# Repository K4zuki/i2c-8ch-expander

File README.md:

# i2c-8ch-expander
8-channel I2C mux, works at 125C

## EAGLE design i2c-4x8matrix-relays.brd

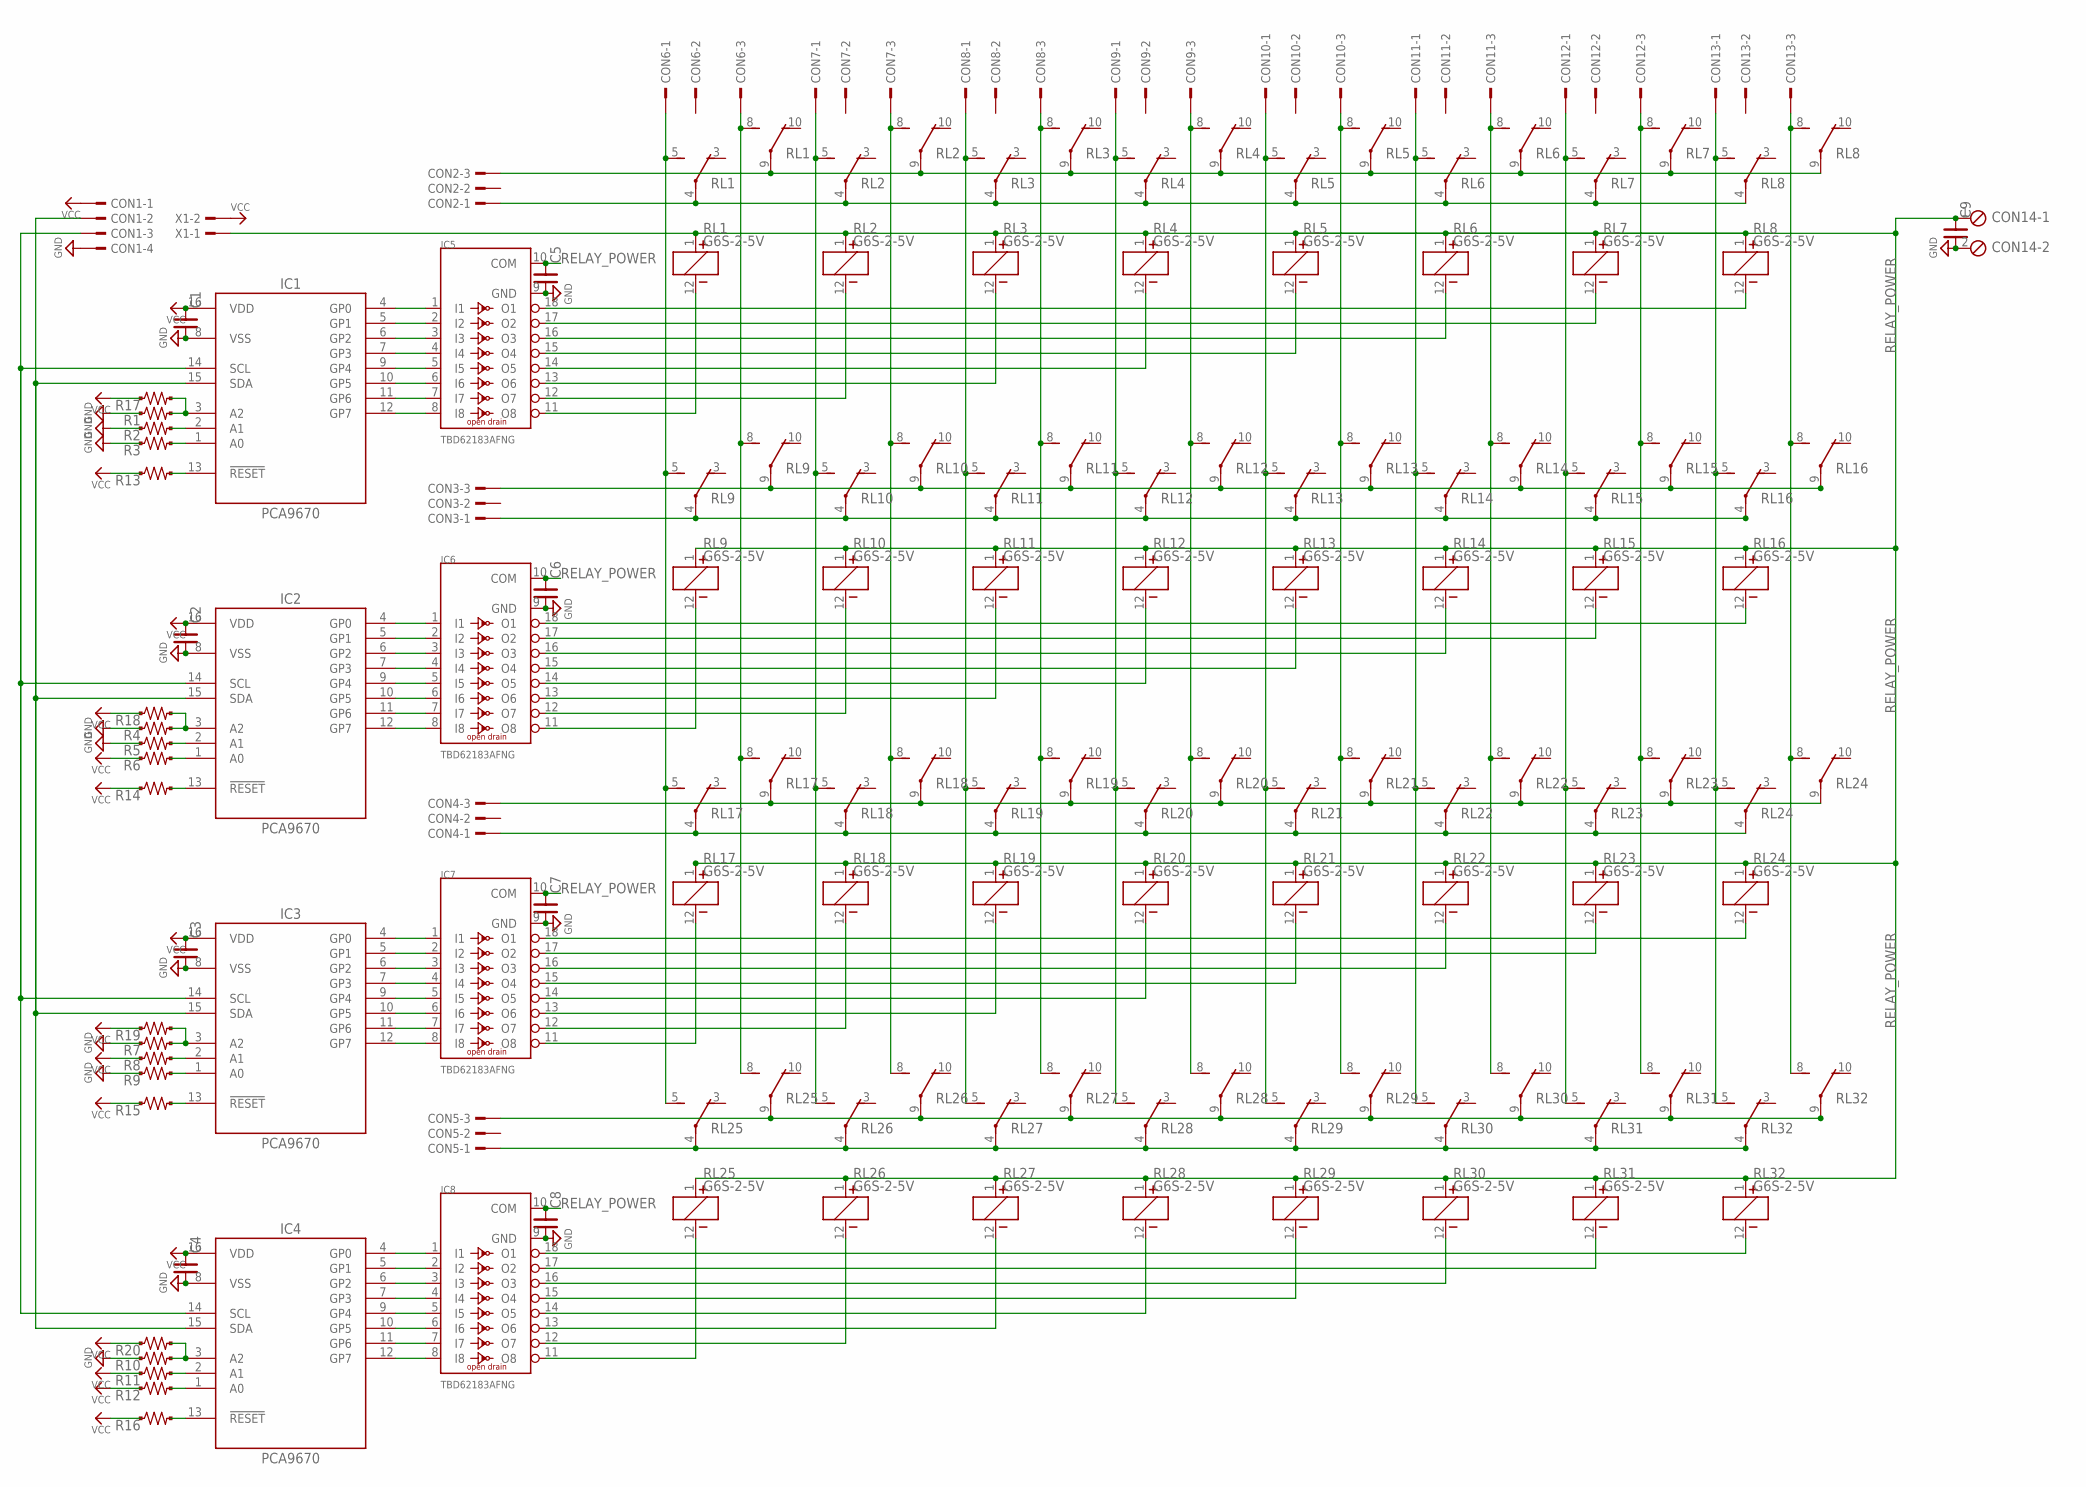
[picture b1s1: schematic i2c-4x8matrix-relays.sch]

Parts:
C1, C2, C3, C4, C5, C6, C7, C8: C-SMD-0.1U-1005; C0402
C9: C-SMD-10U-1608; CR-1608
CON1: S4B-XH-A; S4B-XH-A(LF)(SN)
CON2, CON3, CON4, CON5, CON6, CON7, CON8, CON9, CON10, CON11, CON12, CON13: S3B-XH-A; S3B-XH-A(LF)(SN)
CON14: ETB43024B; ETB43024
IC1, IC2, IC3, IC4: PCA9670; SOT65P510X450X110-16N
IC5, IC6, IC7, IC8: TBD62183AFNG; SOT65P640X440-18N
R1, R2, R3, R4, R5, R6, R7, R8, R9, R10, R11, R12, R13, R14, R15, R16: R-US--1005SHORT; R0402SHORT
R17, R18, R19, R20: R-US-10K-1005; C0402
RL1, RL2, RL3, RL4, RL5, RL6, RL7, RL8, RL9, RL10, RL11, RL12, RL13, RL14, RL15, RL16, RL17, RL18, RL19, RL20, RL21, RL22, RL23, RL24, RL25, RL26, RL27, RL28, RL29, RL30, RL31, RL32: G6S-2-5V; G6S-2
X1: PH-1X2SG

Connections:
GND: C1.2, C2.2, C3.2, C4.2, C5.2, C6.2, C7.2, C8.2, C9.2, CON1.4, CON14.2, IC1.8 (VSS), IC2.8 (VSS), IC3.8 (VSS), IC4.8 (VSS), IC5.9 (GND), IC6.9 (GND), IC7.9 (GND), IC8.9 (GND), R1.1, R1.2 (1), R2.1, R2.2 (1), R3.1, R3.2 (1), R4.1, R4.2 (1), R5.1, R5.2 (1), R7.1, R7.2 (1), R9.1, R9.2 (1), R10.1, R10.2 (1)
unnamed: CON3.1, RL9.4 (COM), RL10.4 (COM), RL11.4 (COM), RL12.4 (COM), RL13.4 (COM), RL14.4 (COM), RL15.4 (COM), RL16.4 (COM)
unnamed: CON4.1, RL17.4 (COM), RL18.4 (COM), RL19.4 (COM), RL20.4 (COM), RL21.4 (COM), RL22.4 (COM), RL23.4 (COM), RL24.4 (COM)
unnamed: CON2.1, RL1.4 (COM), RL2.4 (COM), RL3.4 (COM), RL4.4 (COM), RL5.4 (COM), RL6.4 (COM), RL7.4 (COM), RL8.4 (COM)
unnamed: CON2.3, RL1.9 (COM), RL2.9 (COM), RL3.9 (COM), RL4.9 (COM), RL5.9 (COM), RL6.9 (COM), RL7.9 (COM), RL8.9 (COM)
unnamed: CON6.1, RL1.5 (NO), RL9.5 (NO), RL17.5 (NO), RL25.5 (NO)
unnamed: CON7.1, RL2.5 (NO), RL10.5 (NO), RL18.5 (NO), RL26.5 (NO)
unnamed: CON3.3, RL9.9 (COM), RL10.9 (COM), RL11.9 (COM), RL12.9 (COM), RL13.9 (COM), RL14.9 (COM), RL15.9 (COM), RL16.9 (COM)
unnamed: CON4.3, RL17.9 (COM), RL18.9 (COM), RL19.9 (COM), RL20.9 (COM), RL21.9 (COM), RL22.9 (COM), RL23.9 (COM), RL24.9 (COM)
unnamed: IC8.18 (O1), RL32.12 (2)
unnamed: IC8.11 (O8), RL25.12 (2)
unnamed: CON8.1, RL3.5 (NO), RL11.5 (NO), RL19.5 (NO), RL27.5 (NO)
unnamed: CON9.1, RL4.5 (NO), RL12.5 (NO), RL20.5 (NO), RL28.5 (NO)
unnamed: IC1.4 (GP0), IC5.1 (I1)
unnamed: IC1.5 (GP1), IC5.2 (I2)
unnamed: IC1.6 (GP2), IC5.3 (I3)
unnamed: CON6.3, RL1.8 (NO), RL9.8 (NO), RL17.8 (NO), RL25.8 (NO)
unnamed: IC1.7 (GP3), IC5.4 (I4)
unnamed: IC1.9 (GP4), IC5.5 (I5)
unnamed: IC7.11 (O8), RL17.12 (2)
unnamed: CON7.3, RL2.8 (NO), RL10.8 (NO), RL18.8 (NO), RL26.8 (NO)
unnamed: CON9.3, RL4.8 (NO), RL12.8 (NO), RL20.8 (NO), RL28.8 (NO)
unnamed: CON8.3, RL3.8 (NO), RL11.8 (NO), RL19.8 (NO), RL27.8 (NO)
unnamed: CON5.1, RL25.4 (COM), RL26.4 (COM), RL27.4 (COM), RL28.4 (COM), RL29.4 (COM), RL30.4 (COM), RL31.4 (COM), RL32.4 (COM)
unnamed: CON5.3, RL25.9 (COM), RL26.9 (COM), RL27.9 (COM), RL28.9 (COM), RL29.9 (COM), RL30.9 (COM), RL31.9 (COM), RL32.9 (COM)
unnamed: CON10.1, RL5.5 (NO), RL13.5 (NO), RL21.5 (NO), RL29.5 (NO)
unnamed: CON10.3, RL5.8 (NO), RL13.8 (NO), RL21.8 (NO), RL29.8 (NO)
unnamed: CON11.1, RL6.5 (NO), RL14.5 (NO), RL22.5 (NO), RL30.5 (NO)
unnamed: CON11.3, RL6.8 (NO), RL14.8 (NO), RL22.8 (NO), RL30.8 (NO)
unnamed: CON12.1, RL7.5 (NO), RL15.5 (NO), RL23.5 (NO), RL31.5 (NO)
unnamed: CON12.3, RL7.8 (NO), RL15.8 (NO), RL23.8 (NO), RL31.8 (NO)
unnamed: CON13.1, RL8.5 (NO), RL16.5 (NO), RL24.5 (NO), RL32.5 (NO)
unnamed: CON13.3, RL8.8 (NO), RL16.8 (NO), RL24.8 (NO), RL32.8 (NO)
unnamed: IC1.10 (GP5), IC5.6 (I6)
unnamed: IC7.15 (O4), RL21.12 (2)
unnamed: IC7.18 (O1), RL24.12 (2)
unnamed: IC7.14 (O5), RL20.12 (2)
unnamed: IC7.12 (O7), RL18.12 (2)
unnamed: IC7.13 (O6), RL19.12 (2)
unnamed: IC7.16 (O3), RL22.12 (2)
unnamed: IC7.17 (O2), RL23.12 (2)
unnamed: IC1.11 (GP6), IC5.7 (I7)
unnamed: IC1.12 (GP7), IC5.8 (I8)
unnamed: IC2.4 (GP0), IC6.1 (I1)
unnamed: IC2.5 (GP1), IC6.2 (I2)
unnamed: IC2.6 (GP2), IC6.3 (I3)
unnamed: IC2.7 (GP3), IC6.4 (I4)
unnamed: IC2.9 (GP4), IC6.5 (I5)
unnamed: IC2.10 (GP5), IC6.6 (I6)
unnamed: IC2.11 (GP6), IC6.7 (I7)
unnamed: IC2.12 (GP7), IC6.8 (I8)
unnamed: IC3.4 (GP0), IC7.1 (I1)
unnamed: IC3.5 (GP1), IC7.2 (I2)
unnamed: IC3.6 (GP2), IC7.3 (I3)
unnamed: IC3.7 (GP3), IC7.4 (I4)
unnamed: IC3.9 (GP4), IC7.5 (I5)
unnamed: IC3.10 (GP5), IC7.6 (I6)
unnamed: IC3.11 (GP6), IC7.7 (I7)
unnamed: IC3.12 (GP7), IC7.8 (I8)
unnamed: IC4.4 (GP0), IC8.1 (I1)
unnamed: IC4.5 (GP1), IC8.2 (I2)
unnamed: IC4.6 (GP2), IC8.3 (I3)
unnamed: IC4.7 (GP3), IC8.4 (I4)
unnamed: IC4.9 (GP4), IC8.5 (I5)
unnamed: IC4.10 (GP5), IC8.6 (I6)
unnamed: IC4.11 (GP6), IC8.7 (I7)
unnamed: IC4.12 (GP7), IC8.8 (I8)
unnamed: IC8.17 (O2), RL31.12 (2)
unnamed: IC8.12 (O7), RL26.12 (2)
unnamed: CON1.3, IC1.14 (SCL), IC2.14 (SCL), IC3.14 (SCL), IC4.14 (SCL)
unnamed: CON1.2, IC1.15 (SDA), IC2.15 (SDA), IC3.15 (SDA), IC4.15 (SDA)
unnamed: IC8.13 (O6), RL27.12 (2)
unnamed: IC8.14 (O5), RL28.12 (2)
unnamed: IC8.15 (O4), RL29.12 (2)
unnamed: IC8.16 (O3), RL30.12 (2)
unnamed: IC4.1 (A0), R12.3 (2)
unnamed: IC4.2 (A1), R11.3 (2)
unnamed: IC4.3 (A2), R10.3 (2), R20.2
unnamed: IC3.1 (A0), R9.3 (2)
unnamed: IC3.2 (A1), R8.3 (2)
unnamed: IC3.3 (A2), R7.3 (2), R19.2
unnamed: IC2.1 (A0), R6.3 (2)
unnamed: IC2.2 (A1), R5.3 (2)
unnamed: IC2.3 (A2), R4.3 (2), R18.2
unnamed: IC1.1 (A0), R3.3 (2)
unnamed: IC1.2 (A1), R2.3 (2)
unnamed: IC1.3 (A2), R1.3 (2), R17.2
unnamed: IC1.13 (!RESET!), R13.3 (2)
unnamed: IC2.13 (!RESET!), R14.3 (2)
unnamed: IC3.13 (!RESET!), R15.3 (2)
unnamed: IC4.13 (!RESET!), R16.3 (2)
unnamed: IC6.11 (O8), RL9.12 (2)
unnamed: IC6.12 (O7), RL10.12 (2)
unnamed: IC6.13 (O6), RL11.12 (2)
unnamed: IC6.14 (O5), RL12.12 (2)
unnamed: IC6.15 (O4), RL13.12 (2)
unnamed: IC6.16 (O3), RL14.12 (2)
unnamed: IC6.17 (O2), RL15.12 (2)
unnamed: IC6.18 (O1), RL16.12 (2)
unnamed: IC5.11 (O8), RL1.12 (2)
unnamed: IC5.12 (O7), RL2.12 (2)
unnamed: IC5.13 (O6), RL3.12 (2)
unnamed: IC5.14 (O5), RL4.12 (2)
unnamed: IC5.15 (O4), RL5.12 (2)
unnamed: IC5.16 (O3), RL6.12 (2)
unnamed: IC5.17 (O2), RL7.12 (2)
unnamed: IC5.18 (O1), RL8.12 (2)
RELAY_POWER: C5.1, C6.1, C7.1, C8.1, C9.1, CON14.1, IC5.10 (COM), IC6.10 (COM), IC7.10 (COM), IC8.10 (COM), RL1.1, RL2.1, RL3.1, RL4.1, RL5.1, RL6.1, RL7.1, RL8.1, RL9.1, RL10.1, RL11.1, RL12.1, RL13.1, RL14.1, RL15.1, RL16.1, RL17.1, RL18.1, RL19.1, RL20.1, RL21.1, RL22.1, RL23.1, RL24.1, RL25.1, RL26.1, RL27.1, RL28.1, RL29.1, RL30.1, RL31.1, RL32.1, X1.1
VCC: C1.1, C2.1, C3.1, C4.1, CON1.1, IC1.16 (VDD), IC2.16 (VDD), IC3.16 (VDD), IC4.16 (VDD), R6.1, R6.2 (1), R8.1, R8.2 (1), R11.1, R11.2 (1), R12.1, R12.2 (1), R13.1, R13.2 (1), R14.1, R14.2 (1), R15.1, R15.2 (1), R16.1, R16.2 (1), R17.1, R18.1, R19.1, R20.1, X1.2

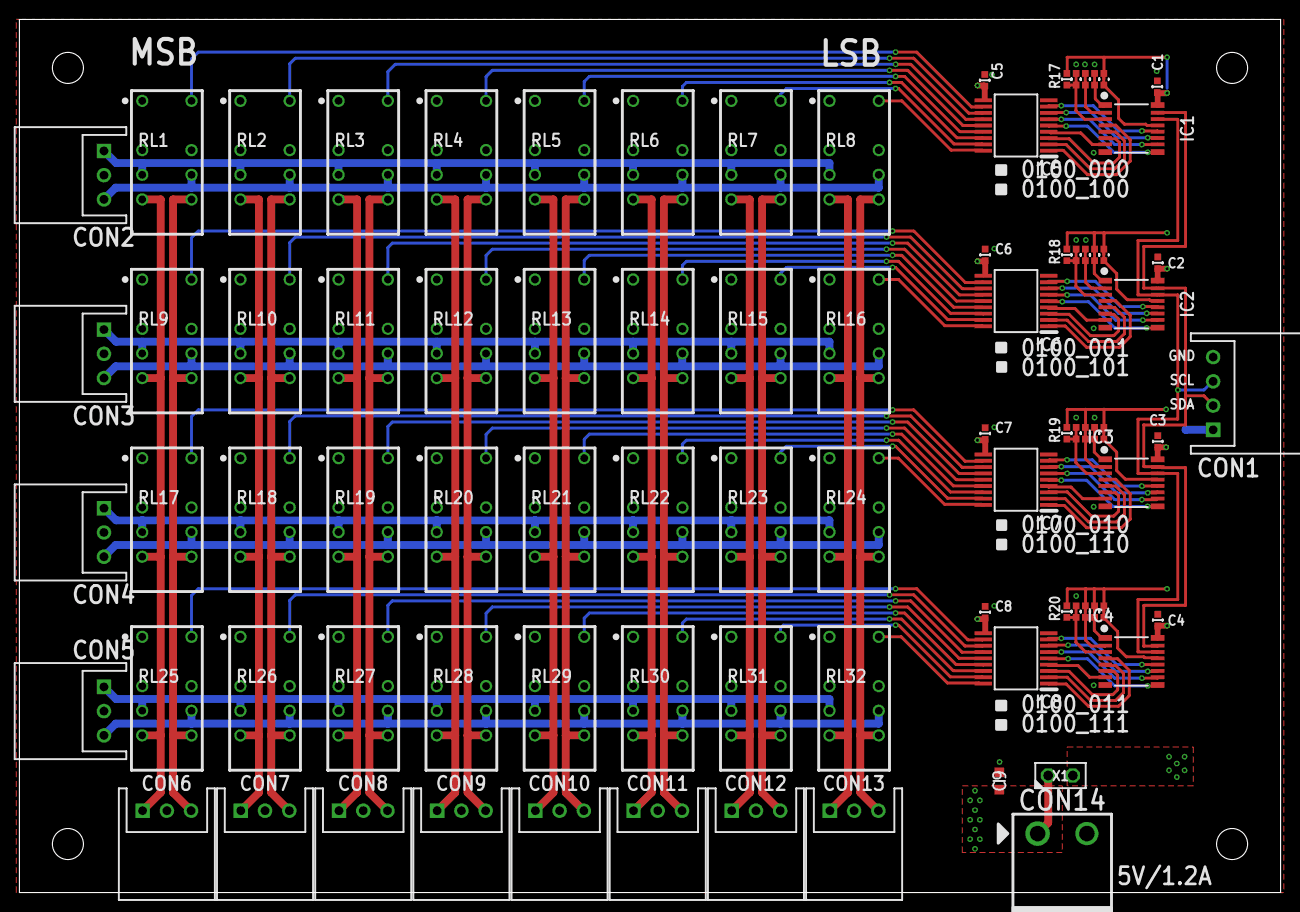
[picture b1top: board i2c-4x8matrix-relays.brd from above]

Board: 2 copper layers, 130.0 x 90.0 mm, 84 parts (0 on the bottom side), 109 nets.

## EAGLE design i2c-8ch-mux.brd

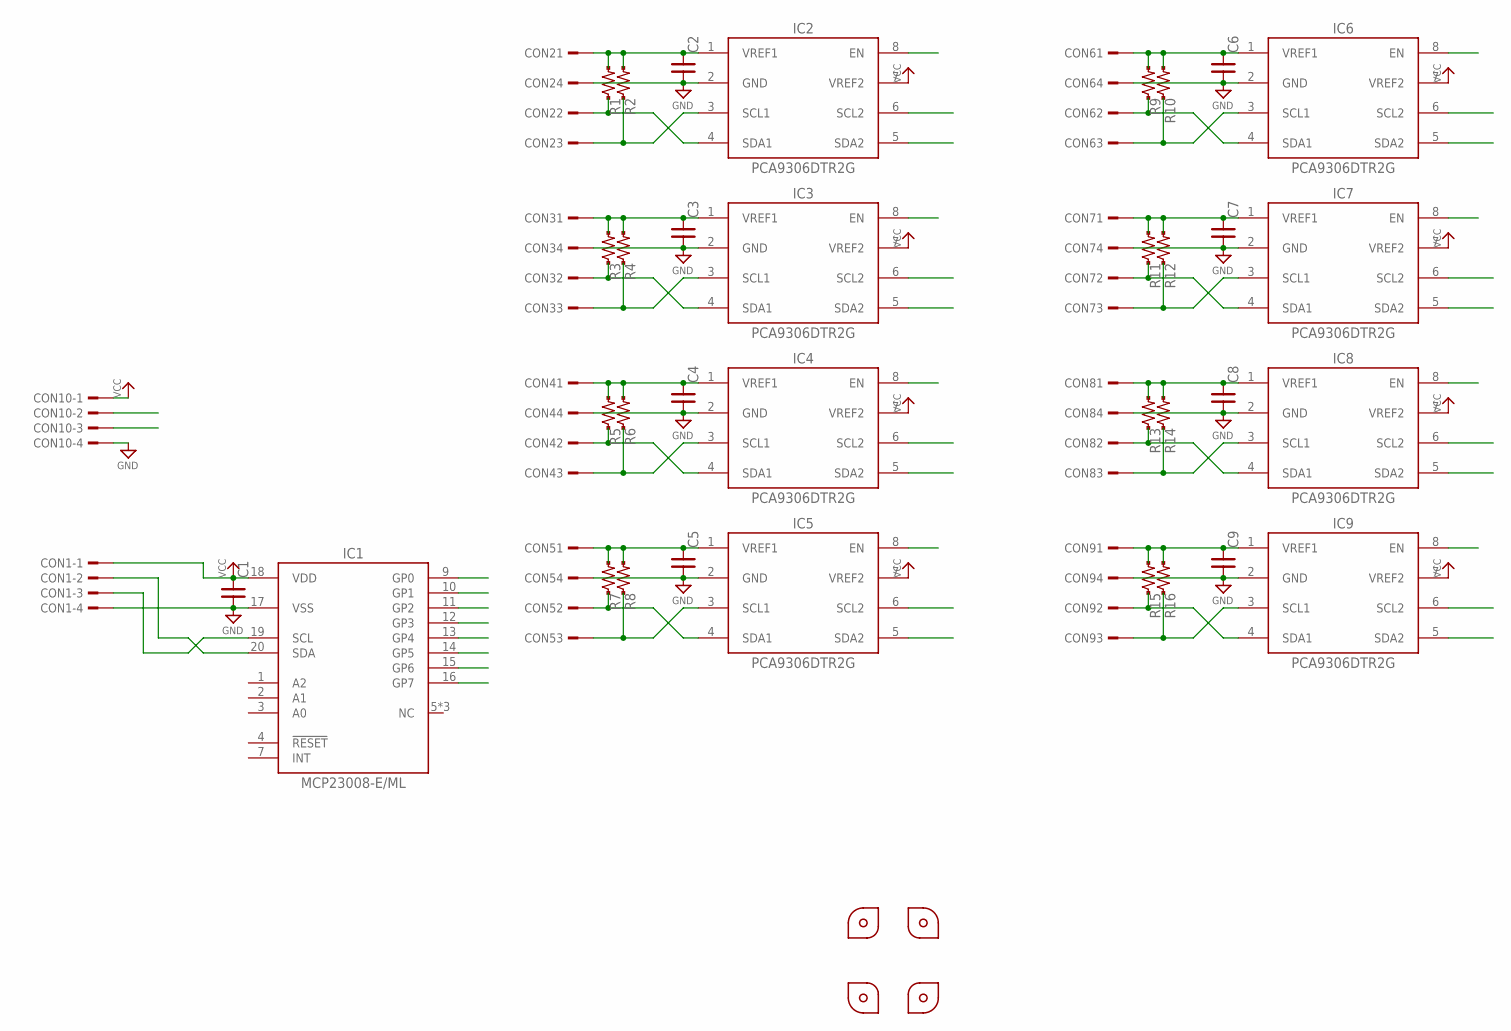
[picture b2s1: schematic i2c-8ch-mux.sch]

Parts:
C1, C2, C3, C4, C5, C6, C7, C8, C9: C-SMD-0.1U-1005; C0402
CON1, CON10: S4B-XH-A; S4B-XH-A(LF)(SN)
CON2, CON3, CON4, CON5, CON6, CON7, CON8, CON9: B4B-XH-A; B4B-XH-A(LF)(SN)
IC1: MCP23008-E/ML; QFN20-0.5P4.0X4.0
IC2, IC3, IC4, IC5, IC6, IC7, IC8, IC9: PCA9306DTR2G; SOT65P440X300-8N
P1, P2, P3, P4: PCB-CORNER
R1, R2, R3, R4, R5, R6, R7, R8, R9, R10, R11, R12, R13, R14, R15, R16: R-US-10K-1005; C0402

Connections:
GND: C1.2, C2.2, C3.2, C4.2, C5.2, C6.2, C7.2, C8.2, C9.2, CON1.4, CON2.4, CON3.4, CON4.4, CON5.4, CON6.4, CON7.4, CON8.4, CON9.4, CON10.4, IC1.17 (VSS), IC2.2 (GND), IC3.2 (GND), IC4.2 (GND), IC5.2 (GND), IC6.2 (GND), IC7.2 (GND), IC8.2 (GND), IC9.2 (GND)
unnamed: C3.1, CON3.1, IC3.1 (VREF1), R3.2, R4.2
unnamed: CON3.2, IC3.4 (SDA1), R3.1
unnamed: C5.1, CON5.1, IC5.1 (VREF1), R7.2, R8.2
unnamed: C2.1, CON2.1, IC2.1 (VREF1), R1.2, R2.2
unnamed: CON3.3, IC3.3 (SCL1), R4.1
unnamed: IC1.10 (GP1), IC3.8 (EN)
unnamed: IC1.9 (GP0), IC2.8 (EN)
unnamed: IC1.11 (GP2), IC4.8 (EN)
unnamed: CON1.3, CON10.3, IC1.19 (SCL), IC2.6 (SCL2), IC3.6 (SCL2), IC4.6 (SCL2), IC5.6 (SCL2), IC6.6 (SCL2), IC7.6 (SCL2), IC8.6 (SCL2), IC9.6 (SCL2)
unnamed: CON1.2, CON10.2, IC1.20 (SDA), IC2.5 (SDA2), IC3.5 (SDA2), IC4.5 (SDA2), IC5.5 (SDA2), IC6.5 (SDA2), IC7.5 (SDA2), IC8.5 (SDA2), IC9.5 (SDA2)
unnamed: CON2.2, IC2.4 (SDA1), R1.1
unnamed: CON2.3, IC2.3 (SCL1), R2.1
unnamed: C8.1, CON8.1, IC8.1 (VREF1), R13.2, R14.2
unnamed: C9.1, CON9.1, IC9.1 (VREF1), R15.2, R16.2
unnamed: C4.1, CON4.1, IC4.1 (VREF1), R5.2, R6.2
unnamed: CON4.3, IC4.3 (SCL1), R6.1
unnamed: CON4.2, IC4.4 (SDA1), R5.1
unnamed: CON5.2, IC5.4 (SDA1), R7.1
unnamed: CON5.3, IC5.3 (SCL1), R8.1
unnamed: C6.1, CON6.1, IC6.1 (VREF1), R9.2, R10.2
unnamed: CON7.2, IC7.4 (SDA1), R11.1
unnamed: CON7.3, IC7.3 (SCL1), R12.1
unnamed: IC1.12 (GP3), IC5.8 (EN)
unnamed: IC1.13 (GP4), IC6.8 (EN)
unnamed: IC1.14 (GP5), IC7.8 (EN)
unnamed: IC1.15 (GP6), IC8.8 (EN)
unnamed: IC1.16 (GP7), IC9.8 (EN)
unnamed: C7.1, CON7.1, IC7.1 (VREF1), R11.2, R12.2
unnamed: CON6.2, IC6.4 (SDA1), R9.1
unnamed: CON6.3, IC6.3 (SCL1), R10.1
unnamed: CON8.2, IC8.4 (SDA1), R13.1
unnamed: CON8.3, IC8.3 (SCL1), R14.1
unnamed: CON9.2, IC9.4 (SDA1), R15.1
unnamed: CON9.3, IC9.3 (SCL1), R16.1
VCC: C1.1, CON1.1, CON10.1, IC1.18 (VDD), IC2.7 (VREF2), IC3.7 (VREF2), IC4.7 (VREF2), IC5.7 (VREF2), IC6.7 (VREF2), IC7.7 (VREF2), IC8.7 (VREF2), IC9.7 (VREF2)

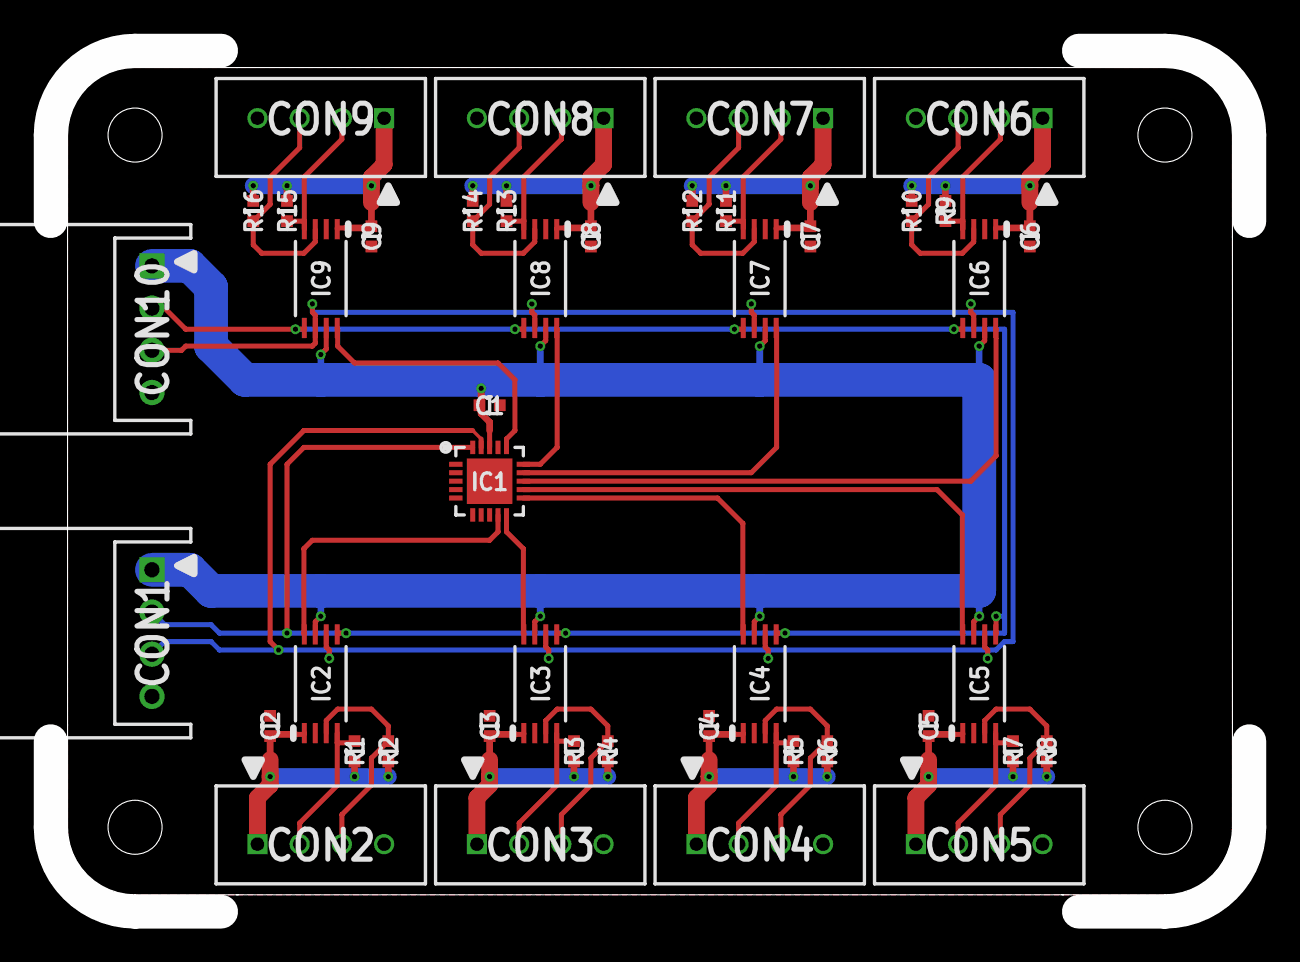
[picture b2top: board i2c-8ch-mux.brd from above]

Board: 2 copper layers, 71.0 x 51.0 mm, 48 parts (0 on the bottom side), 36 nets.

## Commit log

2018-07-13 add submodule
2018-07-14 update submodule
2018-07-14 add board files
2020-12-22 update library
2021-01-30 add 4x8 matrix design
2021-01-30 add matrix board gerber files
2021-06-21 update schematic and layout to use PCA9XXX IO expander
2021-06-21 update library repo
2021-06-21 update gerbers
